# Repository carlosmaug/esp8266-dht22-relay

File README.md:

# ESP8266 model 1  DHT22 or DHT11 realy control

Turns on/off a relay based on reading of temperature and humidity of a DHT22 or DHT11 sensor. Optionally you can turn on/off relay manually using the web interface.

Web interface lets you connect to your wifi, configure defaut values, see DHT readings, turn on/off the relay, and other things.

In this version you will find:
- New Web interface, now responsive.
- New configuration web page added.
- New Relay control page.
- Configuration is kept after reset.
- Fallback to AP mode in case of loosing access to AP.
- Tons of code and circuit testing.
- Added circuit schema.
- All configuration is now placed in a single file.
- Added deug mode to reduce console vervosity.
- Compatibility with esp iot sdk v1.5.4 

Seccurity issues
- MANY.... 
- Wifi password is very easy to retrieve from the web interface.
- No support for ssl nor tls, or any other form of encription.
- No password support.
- It is still pending the use of snprintf.
- ETC..

# Configuration

There are a few parameters that can be changed:
 * include/config.h: Temperature and humidity boundaries to turn on relay, number of  minutes to keey relay on since it was manually turned on, sensor type (DHT11 or DHT22) and poll rate
 
# Building

Make sure the IoT SDK and toolchain are set up according to the instructions on the [ESP8266 wiki](https://github.com/esp8266/esp8266-wiki/wiki/Toolchain). The makefile in this project relies on some environment variables that need to be set. It should be enough to add these to your `.profile`:

	PATH="/opt/Espressif/crosstool-NG/builds/xtensa-lx106-elf/bin/:$PATH"
	export SDK_BASE="/opt/Espressif/ESP8266_SDK"
	export XTENSA_TOOLS_ROOT="/opt/Espressif/crosstool-NG/builds/xtensa-lx106-elf/bin/"
	export ESPTOOL="/opt/Espressif/esptool-py/esptool.py"

From the root of this repository, run `make`. This will build the two firmware images. 

# Screenshots

## Web interface

# Hardware

We have included all information and schemas inside the eagle directory. You can edit them using eagle software.

# Background

This application is based on [Mathew Hall](https://github.com/mathew-hall/esp8266-dht) software, which in turn is based on others, like [Martin's DHT22 webserver](http://harizanov.com/2014/11/esp8266-powered-web-server-led-control-dht22-temperaturehumidity-sensor-reading/) implementation, which uses [sprite_tm's ESP8266 httpd](http://www.esp8266.com/viewtopic.php?f=6&t=376).

# Licenses

Please refer to each file to see the licences.

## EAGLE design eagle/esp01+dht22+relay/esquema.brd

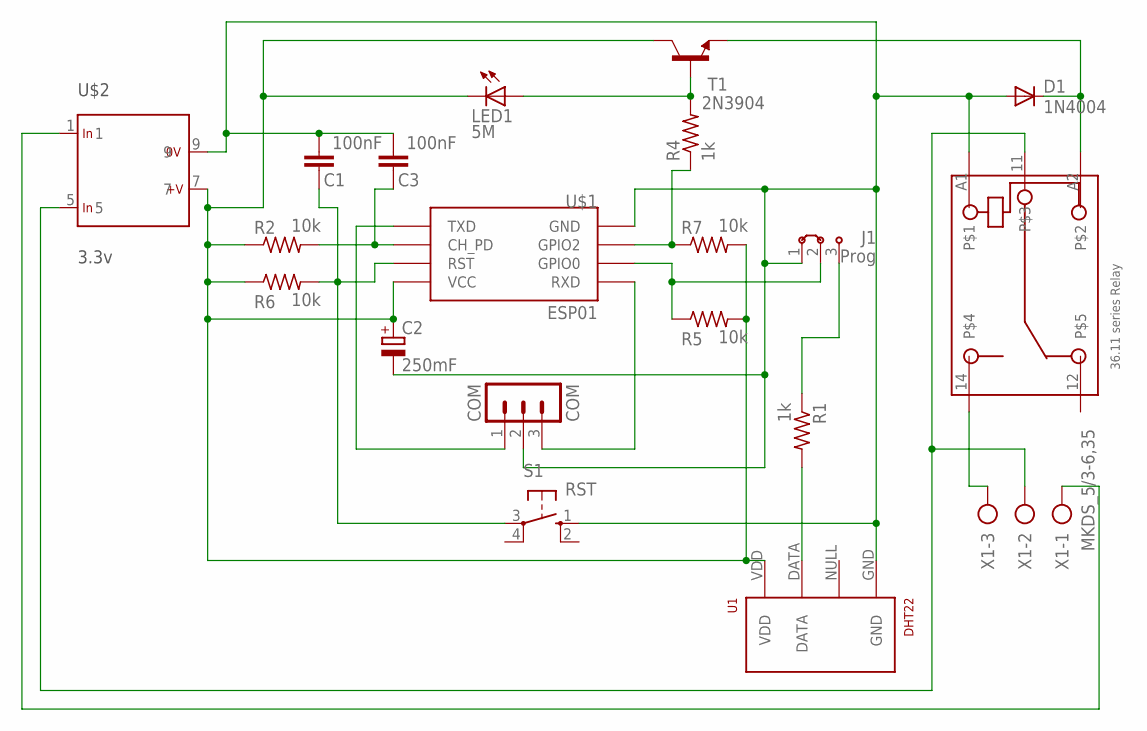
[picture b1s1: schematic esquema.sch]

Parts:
C1, C3: 100nF; CAP-PTH-SMALL-KIT
C2: 250mF; E2-5
COM: COM; MA03-1; MPN 47053-1000
D1: 1N4004; DO41-10; MPN 1N4004-E3/54
J1: Prog; 04C
K1: 36.11
LED1: 5M; LED3MM; MPN HVR3700001504JA100
R1: 1k; 0204/5; MPN MCF 0.25W 1K
R2, R5, R6, R7: 10k; 0204/5; MPN MCF 0.25W 10K
R4: 1k; 0204/5; MPN MCF 0.25W 10K
S1: RST; B3F-10XX
T1: 2N3904; TO92; MPN 2N3904
U1: DHT22; RHT03_DHT-22
U$1: ESP01
U$2: 3.3v; 1; MPN 47121
X1: MKDS_5/3-6,35; MKDS_5/3-635

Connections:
GPI02: R4.1, R7.1, U$1.GPIO2
GPIO0: J1.2, R5.1, U$1.GPIO0
unnamed: D1.C, K1.A2, T1.3 (E)
unnamed: C3.1, R2.2, U$1.CH_PD
unnamed: J1.3, R1.1
unnamed: K1.11, U$2.5, X1.2
unnamed: LED1.A, R4.2, T1.2 (B)
unnamed: R1.2, U1.DATA
unnamed: COM.1, U$1.TX (TXD)
unnamed: COM.3, U$1.RX (RXD)
unnamed: U$2.1, X1.1
unnamed: K1.14, X1.3
RST: C1.1, R6.2, S1.3, U$1.RST
V0: C1.2, C2.-, C3.2, COM.2, D1.A, J1.1, K1.A1, S1.1 (S), U1.GND, U$1.GND, U$2.9
V+: C2.+, LED1.K (C), R2.1, R5.2, R6.1, R7.2, T1.1 (C), U1.VDD, U$1.VCC, U$2.7

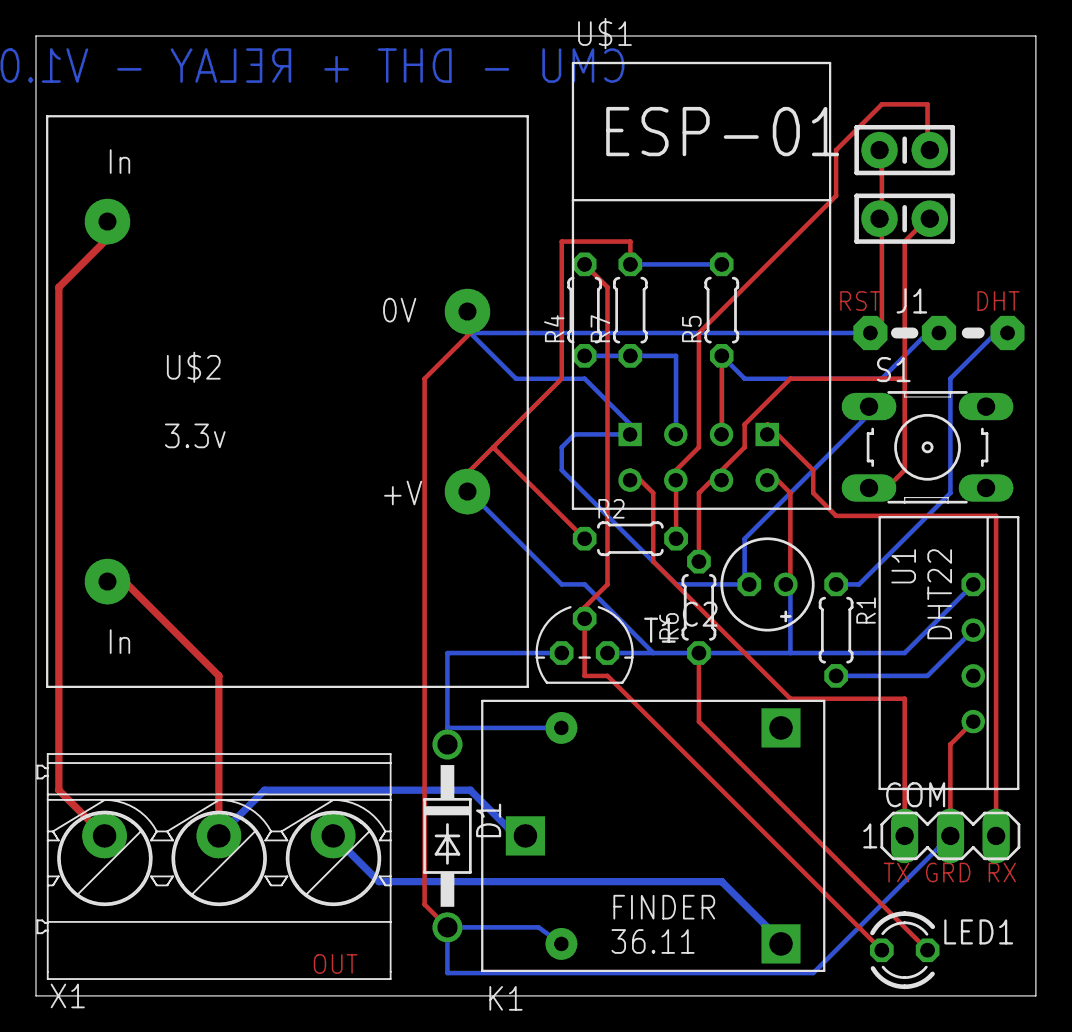
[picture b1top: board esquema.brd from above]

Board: 2 copper layers, 55.5 x 53.3 mm, 20 parts (0 on the bottom side), 15 nets.

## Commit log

2016-05-22 Carga Inicial
2016-05-22 Nada que comentar
2016-05-22 Añadimos imágenes
2016-05-22 Cambio en el tamaño de las imágenes, las hacemos más pequeñas
2016-05-22 Añadimos imagen del esquema
2016-05-22 Hide password
2016-05-22 Ficheros necesarios para la correcta compilación del proyecto
2016-05-22 Necesario para poder imprimir a consola.
2016-05-22 Pequeñas correcciones
2016-06-06 Pasamos a depender de libesphttp
2016-06-06 Pasamos a depender de libesphttpd
2016-06-06 Pequeños cambios
2016-08-15 IO port changed
2016-08-15 IOPORT Change
2016-08-15 Eagle schemas

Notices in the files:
parts and their libraries:
SparkFun-Capacitors: Licensing: Creative Commons ShareAlike 4.0 International - https://creativecommons.org/licenses/by-sa/4.0
